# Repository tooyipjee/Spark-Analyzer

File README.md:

# Spark Analyzer: The Programmable USB-C Power Delivery Analyzer & Power Supply

**Just received your Spark Analyzer? Check out our [quickstart guide](https://www.elektrothing.com/spark-analyzer-quickstart)!**

The **Spark Analyzer** excels in power management. It is a versatile ESP32-powered device tailored for enhancing project development and debugging processes. It is fully compatible with USB-C Power Delivery (PD) and also supports the Programmable Power Supply (PPS) feature, allowing for precise control and management of power. Its compact design facilitates easy inline integration with existing setups, providing essential insights and control over power delivery.

Equipped with WiFi and BLE, the Spark Analyzer offers wireless connectivity, enabling developers to remotely monitor and adjust voltage levels, log data, and analyze power consumption through a user-friendly interface. This design prioritizes convenience and efficiency, removing the need for physical buttons and supporting distance operation.

Fully funded on Crowdsupply [now](https://www.crowdsupply.com/elektrothing/spark-analyzer).

## Features:

1. **Configure USB Power Delivery PD**: When the Spark Analyzer is connected to a USB port that supports Power Delivery (PD), you can configure the output voltage as 5V, 9V, 15V or 20V.

2. **Configure USB Programmable Power Supply PPS**: When the Spark Analyzer is connected to a USB port that supports Programmable Power Supply (PPS), then you can configure the output voltage between 3.3V and 21V in steps of 20 mV. You can also limit the current up to 3A in steps of 50mA.

3. **Power Analysis**: The Spark Analyzer comes with a current sensor. This allows for accurate current draw measurements, essential for understanding power usage in your projects.

4. **Wireless Control**: Untehther your development process with the Spark Analyzer’s wireless capabilities. With both WiFi and BLE, this tool allows remote control and data logging. Users can adjust settings and monitor data from a distance, offering a more flexible development experience.

5. **Open Source & Programmable**: As an open-source device, the Spark Analyzer offers unmatched versatility. It is fully programmable, allowing you to tailor its functionality to your specific applications. This customization extends to software and hardware, opening up endless possibilities for creative and efficient project development.

6. **Compact Design**: Designed for convenience, the Spark Analyzer's compact and sleek form factor allows for seamless integration into existing setups. Its compatibility with USB PD power sources and inline integration capability minimizes the need for additional equipment or extensive redesign, making it a versatile and user-friendly addition to any development environment.

5. **Safety**: Safety is crucial when working with electricity and is at the heart of Spark Analyzer. An integrated output FET allows for software programmable current limit that switches off the power in high-current scenarios.

## Specifications

#### Power
- **Negotiable Power Delivery**: Options of 5 VDC, 9 VDC, 12 VDC, 15 VDC, 20 VDC; max 5 A (100 W at 20 VDC). It is also PPS compatible up to 21 VDC. Note: the Spark Analyzer comes preinstalled with firmware that supports PD. If you want to use PPS you can load this version instead: [WebApp_PPS](https://github.com/tooyipjee/Spark-Analyzer/tree/master/PlatformIO/WebApp_PPS).
- **USB Type-C Port**: For power delivery and integrated JTAG programming.
- **ON Semiconductor [FUSB302MPX](https://www.onsemi.com/pdf/datasheet/fusb302b-d.pdf)**: Programmable USB Type-C control and USB PD communication.
- **ESD Protection**: On D+/D-/CC1/CC2 pins.
- **Texas Instruments [TPS62175DQCT](https://www.ti.com/product/TPS62175/part-details/TPS62175DQCT)**: 3.3 VDC 0.5 A max output DC-DC Step-Down Converter.
- **Power Output**: 3.5 mm, 2-position terminal block.

#### I/O Configuration
- **GPIOs**: 4 GPIOs (I2C, UART, SPI compatible).
- **Power Pins**: 1x 5 VDC and 1x GND.

#### Microcontroller
- **Model**: [ESP32-C3FH4](https://www.espressif.com/sites/default/files/documentation/esp32-c3_datasheet_en.pdf) with 40 MHz crystal.
- **Wi-Fi**: 802.11b/g/n.
- **Bluetooth**: BLE 4.2.
- **Flash Memory**: 4 MB.

#### Interface
- **3x LED Indicators**
  - Power On
  - Output Enable
  - Programmable LED/Debug
- **Buttons**
  - Reset
  - Programmable Button/Debug

#### Programming
- **Integrated JTAG Controller**: For programming.
- **USB-C**: Built-in USB JTAG programmer (ESP32-C3), compatible with Arduino. Select ESP32-C3 Dev Board.

#### Output
- **Current Output**: [CC6904SO-10A](https://datasheet.lcsc.com/lcsc/2304140030_Cross-chip-CC6904SO-10A_C469389.pdf).
- **Current Sensor**: Hall Effect Current Sensor.
- **Output Enable**: [DMP3017SFG-7 FET](https://www.diodes.com/assets/Datasheets/products_inactive_data/DMP3017SFG.pdf).

## Spark Analyzer Mobile App

> **Note**: The Spark Analyzer Mobile App is currently in active development. The features described below are subject to change as we continue to improve the app.

The Spark Analyzer Mobile App, currently done for [Android](https://play.google.com/store/apps/details?id=com.elektrothing.SparkAnalyzer&hl=en&gl=US) (iOS support is available via [RemoteXY](https://apps.apple.com/us/app/remotexy/id1168130280), is the perfect companion to your Spark Analyzer device. It simplifies monitoring and controlling power delivery with these key features:

- **Voltage Selector**: Easily choose from different voltage levels (5 VDC, 9 VDC, 15 VDC, or 20 VDC) using a user-friendly selector.
- **Output Toggle**: Turn the power output on or off conveniently with a toggle switch.
- **Current Logging**: Save current draw as a .csv file.
- **Current Limit**: Ability to set a software current trip as a safety feature.
- **Read-time Display**: View current set point, current draw and output enable in real time on your phone.

### Key Features:

- **Voltage Selector**: The app comes with a user-friendly voltage selector that allows you to easily choose from the different voltage levels supported by the UCPD protocol. Whether you need 5V, 9V, 15V, or 20V, switching between these options is just a tap away.

- **Output Toggle**: Need to turn the power output on or off? The app features a convenient toggle switch that gives you full control over the Spark Analyzer's output, making it simple to manage your device remotely.

- **Current Draw Chart**: Keep an eye on your project's power consumption with the app's real-time current draw chart. This feature provides a graphical representation of the current being drawn, helping you to monitor and optimize your power usage effectively.

### Future Developments:

The Spark Analyzer Mobile App is continuously being improved, with several new features in the pipeline. Upcoming updates will include the ability to export logs for further analysis, set current limits to prevent overcurrent scenarios, and much more.

## Testing for Performance

At the heart of Spark Analyzer's design is a commitment to reliability and performance. To ensure that Spark Analyzer stands up to real-world demands, we subjected it to testing under use conditions.

### Max Current Test: 3A at 9V
Under a load condition of 3A at 9V, Spark Analyzer showcased its robust power delivery capabilities without any hitches.

### Max Voltage Test: 1.5A at 20V
Even at its maximum voltage output of 20V with a 1.5A load, Spark Analyzer continued to perform seamlessly, demonstrating its versatility and reliability.

### Thermal Performance
Safety and efficiency are paramount. We took a thermal image of the board under these testing conditions to ensure that all components remained within safe temperature limits. The results were impressive: the entire board stayed cool, with the warmest component being the ESP32 microcontroller, which only reached around 40°C.

These tests underscore Spark Analyzer's commitment to delivering a product that is not only feature-rich but also reliable, safe, and efficient. With Spark Analyzer, you're investing in a device that's been tried and tested to ensure optimal performance under all conditions.

## Package Contents:

- 1x Spark Analyzer
- Additional components (Specify as per your package)

## Manufacturing & Logistics:

Our designs have undergone rigorous testing and verification. We've already produced a pilot batch, and our manufacturing partners are geared up for full-scale production. All Spark Analyzer units will be shipped globally, ensuring timely delivery to our backers.

## Comparison: Spark Analyzer vs PD Micro vs Lab Power Supply

|    | Spark Analyzer               | [PD Micro](https://www.mouser.co.uk/ProductDetail/Crowd-Supply/CS-PDMICRO-01?qs=TuK3vfAjtkXixx0TeJooNQ%3D%3D)               | [TinyPICO V3](https://www.conrad.com/en/p/joy-it-com-zy12pdn-converter-1-pc-s-2475888.html?WT.srch=1&vat=true&utm_source=google&utm_medium=organic&utm_campaign=shopping&srsltid=AfmBOooPUzUXbytdxZNQd-7snqUbn7jtgCwQktmcI8B5WYmZAfE5yNWl4q0#productDownloads)          | [Joy-IT COM ZY12PDN](https://shop.pimoroni.com/products/tinypico-v2?variant=39285089534035)   |
|------------------------------|------------------------------|------------------------|----------------------|----------------------|
| **Microcontroller**          | ESP32-C3                     | ATmega32U4             | ESP32-PICO-D4        | Not Applicable       |
| **WiFi Connectivity**        | Available (802.11b/g/n)      | Not Available          | Available            | Not Available        |
| **Bluetooth Connectivity**   | Available (BLE 4.2)          | Not Available          | Available            | Not Available        |
| **Flash Memory**             | 4 MB                         | Not Specified          | 4 MB                 | Not Specified        |
| **USB-C Power Delivery**     | Supported                    | Supported              | Not Supported        | Supported            |
| **Output Control**           | Adjustable                   | Adjustable             | Not Specified        | Adjustable           |
| **Wireless Control**         | Yes                          | No                     | Yes                  | No                   |
| **Smartphone App Support**   | Yes                          | No                     | No                   | No                   |
| **Power Analysis**           | Accurate                     | Basic                  | Not Specified        | Basic                |
| **Design**                   | Compact and Sleek            | Compact                | Ultra-Small          | Compact              |
| **Open Source Status**       | Yes                          | Yes                    | Yes                  | No                   |
| **Programming Interface**    | USB + JTAG                   | USB                    | USB                  | Not Applicable       |
| **Inline Integration**       | Yes                          | No                     | Not Applicable       | No                   |
| Power Delivery Range         | 5-20 VDC Supported           | 5-20 VDC Supported     | Not Supported        | 5-20 VDC Supported   |
| **Price (USD)**              | $49                          | $28                    | $22                  | $16                  |

## Firmware development

If you want to modify the functionality of the Spark Analyzer or contribute to it's firmware development process, you can follow the steps below.

* clone this repository `git clone https://github.com/tooyipjee/Spark-Analyzer.git`
* install [Visual Studio Code](https://code.visualstudio.com/Docs/setup/setup-overview)
* install the [PlatformIO](https://platformio.org/) plugin in VSCode
* open the project you want to use: [WebApp for Power Delivery](https://github.com/tooyipjee/Spark-Analyzer/tree/master/PlatformIO/WebApp) or [WebApp for Programmable Power Supply](https://github.com/tooyipjee/Spark-Analyzer/tree/master/PlatformIO/WebApp_PPS)
* connect the Spark Analyzer with a usb-C to usb-C cable to your computer
* open the "Monitor" task in PlatformIO
  * you may have to configure the serial port in `platformio.ini` file, e.g.
  ```
    upload_port = /dev/ttyACM0
    monitor_port = /dev/ttyACM0
  ```
* make sure you see the boot messages
* perform the "Build" task to build the firmware
* then perform the "Upload" task to flash the new firmware
* once the flashing is complete, perform "Build Filesystem Image" and "Upload Filesystem Image" tasks

### Debugging

* in the Platform IO "Monitor" you can follow the debug output from the Spark Analyzer
* if you have a serial UART adapter you can also
  * connect to the GND, RX, TX pins to the Spark Analyzer and
  * change the `UART` marcro in `main.cpp` to use `Serial0`
  * then you can see some debug output via this second UART

## Web development

* The web app is served from the data/index.html file
* You can follow the requests and responses exchanged between the web app and the firmware by opening your browser's "Web Development Tools".

## Mobile app development

See flutter/SparkAnalyzer/README.md

## License

MIT License

Copyright (c) 2023 elektroThing

Permission is hereby granted, free of charge, to any person obtaining a copy
of this software and associated documentation files (the "Software"), to deal
in the Software without restriction, including without limitation the rights
to use, copy, modify, merge, publish, distribute, sublicense, and/or sell
copies of the Software, and to permit persons to whom the Software is
furnished to do so, subject to the following conditions:

The above copyright notice and this permission notice shall be included in all
copies or substantial portions of the Software.

THE SOFTWARE IS PROVIDED "AS IS", WITHOUT WARRANTY OF ANY KIND, EXPRESS OR
IMPLIED, INCLUDING BUT NOT LIMITED TO THE WARRANTIES OF MERCHANTABILITY,
FITNESS FOR A PARTICULAR PURPOSE AND NONINFRINGEMENT. IN NO EVENT SHALL THE
AUTHORS OR COPYRIGHT HOLDERS BE LIABLE FOR ANY CLAIM, DAMAGES OR OTHER
LIABILITY, WHETHER IN AN ACTION OF CONTRACT, TORT OR OTHERWISE, ARISING FROM,
OUT OF OR IN CONNECTION WITH THE SOFTWARE OR THE USE OR OTHER DEALINGS IN THE
SOFTWARE.

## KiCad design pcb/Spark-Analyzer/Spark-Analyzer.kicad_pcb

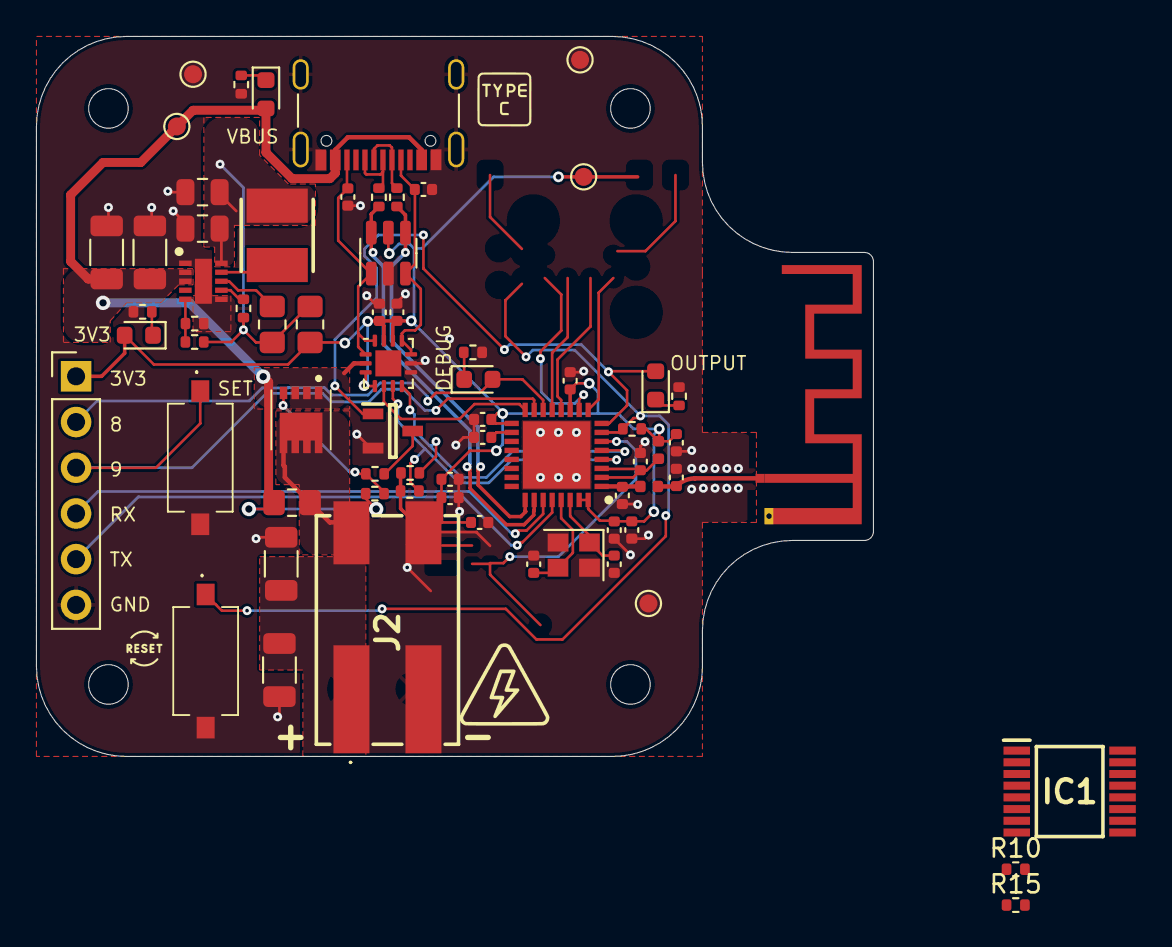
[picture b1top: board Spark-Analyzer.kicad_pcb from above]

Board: 4 copper layers, 46.5 x 40.0 mm, 75 parts (1 on the bottom side), 39 nets.

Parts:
 : LOGO; highVoltage
 #2: LOGO; highVoltage
AE2: Antenna; Texas_SWRA117D_2.4GHz_Left
C1, C20, C21, C22: 10u_1206; C_1206_3216Metric
C2: 22u; C_0805_2012Metric
C3: 10u; C_0805_2012Metric
C4, C5: 100p; C_0402_1005Metric
C6, C7, C14, C16, C17, C18, C19, C24, C25: 100n; C_0402_1005Metric
C9, C12: 20p; C_0402_1005Metric
C10: 4p; C_0402_1005Metric
C11: 5p; C_0402_1005Metric
C13, C15: 1u; C_0402_1005Metric
C23: 10u_0402; C_0402_1005Metric
D1, D2, D4: Green_0603; LED_0603_1608Metric
D3: Yellow_0603; LED_0603_1608Metric
H1, H2, H3, H4: MountingHole; MountingHole_2.2mm_M2
IC1: INA260AIPWR; SOP65P640X120-16N
IC2: FUSB302MPX; WQFN-14-1EP_2.5x2.5mm_P0.5mm_EP1.45x1.45mm
IC4: TPS62175DQCT; SON50P200X300X80-11N
IC5: ESP32-C3FH4; QFN50P500X500X90-33N-D
J1: GT-USB-7010; GT-USB-7010A
J2: 2060-452_998-404; 2060452998404
J5: Conn_01x06; PinHeader_1x06_P2.54mm_Vertical
L1: 10uH; INDPM4040X300N
L2, L3: 1.8nH; L_0402_1005Metric
Q1: DTC143ECA-TP; SOT95P237X125-3N
Q2: DMP3017SFG-7; DMP3007SFG7
R1: 100k; R_0402_1005Metric
R2: 1M2; R_0402_1005Metric
R3: 383k; R_0402_1005Metric
R4, R5: 0; R_0805_2012Metric_Pad1.20x1.40mm_HandSolder
R6, R7: 22; R_0402_1005Metric
R10, R12, R13, R14, R15, R19: 10k; R_0402_1005Metric
R16, R17, R18, R22: 2.7k; R_0402_1005Metric
R20: 1k; R_0402_1005Metric
R21: DNF_0805; R_0805_2012Metric_Pad1.20x1.40mm_HandSolder
S1, S2: TS-1101-C-W; TS1101CW
TP3, TP4, TP5, TP10, TP11: TestPoint; TestPoint_Pad_D1.0mm
U1: SRV05-4; SOT-23-6
Y2: SX25Y040000BF1T-C; Crystal_SMD_2520-4Pin_2.5x2.0mm

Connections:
+3V3: C6.2, C7.1, C13.1, C14.2, C16.1, C17.1, C18.1, C23.1, C24.2, C25.2, D1.2 (A), IC1.10 (VS), IC2.3 (VDD_1), IC2.4 (VDD_2), IC2.12 (VCONN_1), IC2.13 (VCONN_2), IC5.11 (VDD3P3_RTC), IC5.17 (VDD3P3_CPU), IC5.31 (VDDA_1), IC5.32 (VDDA_2), J5.1, L3.2, R4.2, R12.1, R13.1, R14.1, TP3.1, U1.5 (VP)
/Current Sensor + Output Control/VOUT: C1.1, C22.1, IC1.14 (IN-_1), IC1.15 (IN-_2), IC1.16 (IN-_3), J2.1 (1.1)
/Microcontroller/EN: IC5.7 (CHIP_EN), R12.2, S1.1
/Microcontroller/GPIO0: IC1.9 (SCL), IC2.6 (SCL), IC5.4 (XTAL_32K_P), R14.2
/Microcontroller/GPIO1: IC1.8 (SDA), IC2.7 (SDA), IC5.5 (XTAL_32K_N), R13.2
/Microcontroller/GPIO3: D3.2 (A), IC5.8 (GPIO3), Q1.1
/Microcontroller/GPIO8: D4.2 (A), IC5.14 (GPIO8), J5.2
/Microcontroller/GPIO9: IC5.15 (GPIO9), J5.3, S2.1
/Microcontroller/INT_N: IC2.5 (INT_N), IC5.16 (GPIO10)
/Microcontroller/U0RXD: IC5.27 (U0RXD), J5.4
/Microcontroller/U0TXD: IC5.28 (U0TXD), J5.5
/Microcontroller/USB_DN: IC5.25 (GPIO18), R6.2, U1.4 (IO3)
/Microcontroller/USB_DP: IC5.26 (GPIO19), R7.1, U1.6 (IO4)
/Microcontroller/VDD_SPI: C15.1, IC5.18 (VDD_SPI)
GND: C1.2, C2.2, C3.2, C4.2, C5.2, C6.1, C7.2, C9.2, C10.2, C11.2, C12.1, C13.2, C14.1, C15.2, C16.2, C17.2, C18.2, C19.2, C20.2, C21.2, C22.2, C23.2, C24.1, C25.1, IC1.6 (GND_1), IC1.11 (GND_2), IC2.8 (GND_1), IC2.9 (GND_2), IC4.1 (PGND), IC4.6 (AGND), IC4.11 (EP), IC5.33 (EP), J1.A1 (GND), J1.B1 (GND), J1.S1 (SHIELD), J2.3 (2.1), J5.6, Q1.2, R3.2, R10.2, R15.2, R16.2, R17.2, R18.2, R22.2, S1.2, S2.2, TP5.1, TP10.1, TP11.1, U1.2 (VN), Y2.2, Y2.4
unnamed: AE2.1 (A), C10.1, L2.1
unnamed: D1.1 (K), R16.1
unnamed: D2.1 (K), R17.1
unnamed: D3.1 (K), R18.1
unnamed: D4.1 (K), R22.1
unnamed: IC1.5 (A0), R15.1
unnamed: IC1.4 (A1), R10.1
unnamed: IC1.1 (IN+_1), IC1.2 (IN+_2), IC1.3 (IN+_3), Q2.5 (D_1), Q2.6, Q2.7, Q2.8, Q2.9, R21.2
unnamed: C5.1, IC2.10 (CC1_1), IC2.11 (CC1_2), J1.A5 (CC1), U1.3 (IO2)
unnamed: C4.1, IC2.1 (CC2_1), IC2.14 (CC2_2), J1.B5 (CC2), U1.1 (IO1)
unnamed: IC4.5 (FB), R2.2, R3.1
unnamed: IC4.7 (PG), R1.2
unnamed: IC4.8 (SLEEP), R5.1
unnamed: IC4.9 (SW), L1.1
unnamed: C2.1, C3.1, IC4.10 (VOS), L1.2, R1.1, R2.1, R4.1, R5.2
unnamed: C11.1, IC5.1 (LNA_IN), L2.2
unnamed: C19.1, IC5.2 (VDD3P3_1), IC5.3 (VDD3P3_2), L3.1
unnamed: C12.2, IC5.29 (XTAL_N), Y2.3
unnamed: C9.1, IC5.30 (XTAL_P), Y2.1
unnamed: J1.A6 (D+), J1.B6 (D+), R7.2
unnamed: J1.A7 (D-), J1.B7 (D-), R6.1
unnamed: Q1.3, R20.2
unnamed: Q2.4 (G), R19.2, R20.1
VBUS: C20.1, C21.1, D2.2 (A), IC1.12 (VBUS), IC2.2 (VBUS), IC4.2 (VIN), IC4.3 (EN), J1.A4 (VBUS), J1.A9 (VBUS), J1.B4 (VBUS), J1.B9 (VBUS), Q2.1, Q2.2, Q2.3, R19.1, R21.1, TP4.1

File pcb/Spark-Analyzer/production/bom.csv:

Designator,Footprint,Quantity,Value,LCSC Part #
AE2,Texas_SWRA117D_2.4GHz_Left,1,Antenna,
"C1, C20, C21, C22",1206,4,10u_1206,C466808
C10,0402,1,4p,C311704
C11,0402,1,5p,C1573
"C12, C9",0402,2,20p,C1554
"C13, C15",0402,2,1u,C52923
"C14, C16, C17, C18, C19, C24, C25, C6, C7, C8",0402,10,100n,C307331
C2,0805,1,22u,C602037
C23,0402,1,10u_0402,C315248
C3,0805,1,10u,C15850
"C4, C5",0402,2,100p,C1546
"D1, D2, D4",0603,3,Green_0603,C72043
D3,0603,1,Yellow_0603,C72038
"H1, H2, H3, H4",MountingHole_2.2mm_M2,4,MountingHole,
IC2,WQFN-14-1EP_2.5x2.5mm_P0.5mm_EP1.45x1.45mm,1,FUSB302MPX,C442699
IC3,SOP-8_3.9x4.9mm_P1.27mm,1,CC6904SO-10A,C469389
IC4,SON50P200X300X80-11N,1,TPS62175DQCT,C32097
IC5,QFN50P500X500X90-33N-D,1,ESP32-C3FH4,C2858491
J1,GT-USB-7010A,1,GT-USB-7010,C963370
J2,TC2050-IDC,1,TC2050-IDC,
J3,KF350352P,1,KF350-3.5-2P,C474892
J5,PinHeader_1x06_P2.54mm_Vertical,1,Conn_01x06,C492405
L1,INDPM4040X300N,1,10uH,C38117
"L2, L3",0402,2,1.8nH,
Q1,SOT95P237X125-3N,1,DTC143ECA-TP,
Q2,DMP3007SFG7,1,DMP3017SFG-7,DMP3017SFG
R1,0402,1,100k,C25741
"R11, R4, R5, R9",0805,4,0,C17477
"R12, R13, R14, R19",0402,4,10k,C25744
"R16, R17, R18, R22",0402,4,2.7k,C25885
R2,0402,1,1M2,C413030
R20,0402,1,1k,C11702
R21,0805,1,DNF_0805,
R3,0402,1,383k,C163468
"R6, R7",0402,2,22,C25092
R8,0402,1,100,C25076
"S1, S2",TS1101CW,2,TS-1101-C-W,C318938
"TP10, TP11, TP3, TP4, TP5, TP8",TestPoint_Pad_D1.0mm,6,TestPoint,
U1,SOT-23-6,1,SRV05-4,
Y2,Crystal_SMD_2520-4Pin_2.5x2.0mm,1,SX25Y040000BF1T-C,C271649

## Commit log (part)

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2023-03-05 done SCH review and layout placement
2023-03-18 finished layout
2023-03-18 changed gpio pins
2023-04-07 powerpod
2023-04-18 created production files
2023-05-14 first pass code
2023-05-19 Updated source code
2023-05-20 Updated code for current measurement
2023-05-21 Updated ble code with current measure
2023-05-21 Commented out printlns
2023-05-21 Updated paths
2023-06-05 Updated code
2023-06-19 Updated files
2023-06-19 Added step file
2023-08-13 Update photos
2023-08-15 Added more images
2023-10-06 Updated name to Spark Analyzer
2023-10-06 Updated with image for app
2023-10-06 Renamed image
2023-10-23 test flutter app
2023-10-23 added two way comms
2023-10-29 Remove graphing and added logging
2023-11-03 First app release and updated PCBA
2023-11-04 Fixed issues with app release
2023-11-07 Added silkscreen symbols and texts
2023-11-14 Added remoteXY code for iOS and created a template project
2023-11-26 Improved stability of app
2024-02-12 create neopixel demo
2024-02-12 updated photos
2024-02-13 Uploaded platformio example
2024-02-18 update matter demo
2024-03-01 update code comments and added web app
2024-03-02 Added PPS functionality
2024-03-31 updated gitignore
2024-04-02 updated template sketch
2024-05-31 created prod firmware
2024-07-22 productions software uploaded
2024-07-22 Switched current sensor
2024-08-03 whitespace cleanup
2024-08-03 README: clarify PD vs PPS
2024-08-03 here -> quickstart guide
2024-08-03 user-friendly smartphone interface -> user-friendly interface
    I was confused initially whether I had to use the app, or I could use the web interface. I think this phrasing should induce less confusion
2024-08-03 whitespace
2024-08-03 note to install PPS firmware
2024-08-08 README + firmware development
2024-08-10 make Serial vs Serial0 configurable
2024-08-10 README+ FW debugging and web/app dev
2024-08-10 printStatus
    and some debug beautification
2024-08-11 rename variables, web api calls, etc to more expressive, e.g. currentSet -> ppsOutputCurrentLimitA
2024-08-11 store PPS values in Preferences
2024-08-12 revert UART to Serial
2024-08-17 log handlePpsOutputState
2024-08-17 rewrite Serial port selection with DEBUG_VIA_DEFAULT_UART
2024-08-18 add USE_WIFI_MANAGER macro for easier ability to hardcode wifi
    mostly useful for developers maybe
2024-08-18 add USE_PD_UFP_LOGGING to enable PD_UFP.print_status
2024-08-18 init_PPS with stored values rather than hardcode 5V, 2A
2024-08-22 Even more verbose PD_UFP logging
2024-08-22 Seems that there is this GitGuardian service in GitHub that flags code that might leak secrets and "flag" means making PR's fail validation Thanks, but no thanks. Make GG stfu about these demo creden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
2024-08-22 Slightly more verbose logging at boot
2024-08-22 away away you go GitGuardian
2024-08-22 ok. I give up GitGuardian wins, I'll make the code harder to use to bow to the overlord
2024-08-22 jumping through hoops
2024-09-21 Wired sensor and changed connector
2024-12-28 To be reviewed
2025-01-03 Create ReadME.md for quickstart
